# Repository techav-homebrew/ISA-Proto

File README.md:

# ISA-Proto
8-bit ISA Protoboard

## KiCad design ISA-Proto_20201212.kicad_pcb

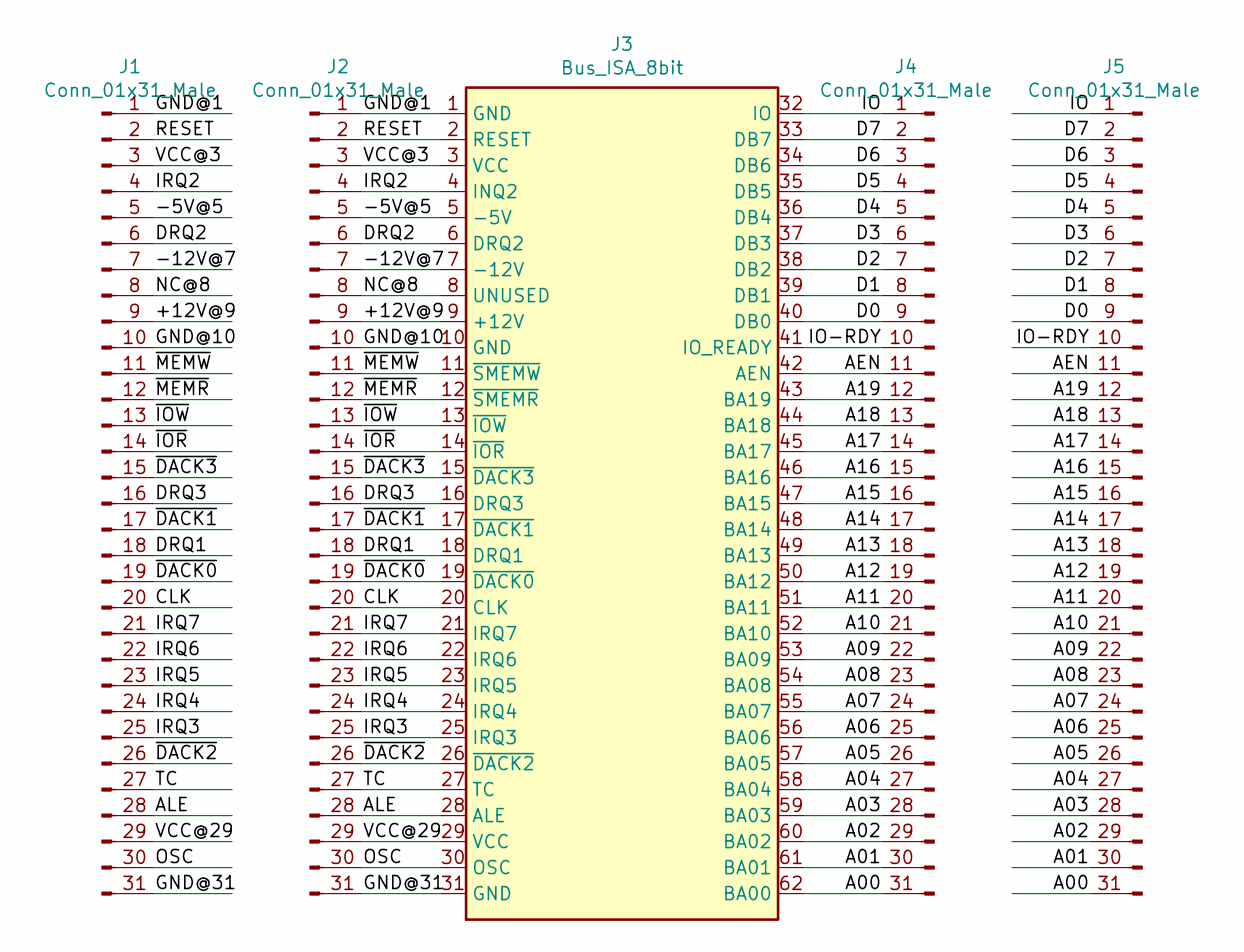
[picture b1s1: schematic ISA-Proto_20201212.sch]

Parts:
J1, J2, J4, J5: Conn_01x31_Male; PinHeader_1x31_P2.54mm_Vertical
J3: Bus_ISA_8bit; BUS_XT

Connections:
/+12V@9: J1.9, J2.9, J3.9 (+12V)
/-5V@5: J1.5, J2.5, J3.5 (-5V)
/-12V@7: J1.7, J2.7, J3.7 (-12V)
/A00: J3.62 (BA00), J4.31, J5.31
/A01: J3.61 (BA01), J4.30, J5.30
/A02: J3.60 (BA02), J4.29, J5.29
/A03: J3.59 (BA03), J4.28, J5.28
/A04: J3.58 (BA04), J4.27, J5.27
/A05: J3.57 (BA05), J4.26, J5.26
/A06: J3.56 (BA06), J4.25, J5.25
/A07: J3.55 (BA07), J4.24, J5.24
/A08: J3.54 (BA08), J4.23, J5.23
/A09: J3.53 (BA09), J4.22, J5.22
/A10: J3.52 (BA10), J4.21, J5.21
/A11: J3.51 (BA11), J4.20, J5.20
/A12: J3.50 (BA12), J4.19, J5.19
/A13: J3.49 (BA13), J4.18, J5.18
/A14: J3.48 (BA14), J4.17, J5.17
/A15: J3.47 (BA15), J4.16, J5.16
/A16: J3.46 (BA16), J4.15, J5.15
/A17: J3.45 (BA17), J4.14, J5.14
/A18: J3.44 (BA18), J4.13, J5.13
/A19: J3.43 (BA19), J4.12, J5.12
/AEN: J3.42 (AEN), J4.11, J5.11
/ALE: J1.28, J2.28, J3.28 (ALE)
/CLK: J1.20, J2.20, J3.20 (CLK)
/D0: J3.40 (DB0), J4.9, J5.9
/D1: J3.39 (DB1), J4.8, J5.8
/D2: J3.38 (DB2), J4.7, J5.7
/D3: J3.37 (DB3), J4.6, J5.6
/D4: J3.36 (DB4), J4.5, J5.5
/D5: J3.35 (DB5), J4.4, J5.4
/D6: J3.34 (DB6), J4.3, J5.3
/D7: J3.33 (DB7), J4.2, J5.2
/DRQ1: J1.18, J2.18, J3.18 (DRQ1)
/DRQ2: J1.6, J2.6, J3.6 (DRQ2)
/DRQ3: J1.16, J2.16, J3.16 (DRQ3)
/GND@1: J1.1, J2.1, J3.1 (GND)
/GND@10: J1.10, J2.10, J3.10 (GND)
/GND@31: J1.31, J2.31, J3.31 (GND)
/IO-RDY: J3.41 (IO_READY), J4.10, J5.10
/IOCHCK: J3.32 (IO), J4.1, J5.1
/IRQ2: J1.4, J2.4, J3.4 (INQ2)
/IRQ3: J1.25, J2.25, J3.25 (IRQ3)
/IRQ4: J1.24, J2.24, J3.24 (IRQ4)
/IRQ5: J1.23, J2.23, J3.23 (IRQ5)
/IRQ6: J1.22, J2.22, J3.22 (IRQ6)
/IRQ7: J1.21, J2.21, J3.21 (IRQ7)
/OSC: J1.30, J2.30, J3.30 (OSC)
/RESET: J1.2, J2.2, J3.2 (RESET)
/TC: J1.27, J2.27, J3.27 (TC)
/VCC@3: J1.3, J2.3, J3.3 (VCC)
/VCC@29: J1.29, J2.29, J3.29 (VCC)
/~CARD: J1.8, J2.8, J3.8 (UNUSED)
/~DACK0: J1.19, J2.19, J3.19 (~DACK0)
/~DACK1: J1.17, J2.17, J3.17 (~DACK1)
/~DACK2: J1.26, J2.26, J3.26 (~DACK2)
/~DACK3: J1.15, J2.15, J3.15 (~DACK3)
/~IOR: J1.14, J2.14, J3.14 (~IOR)
/~IOW: J1.13, J2.13, J3.13 (~IOW)
/~MEMR: J1.12, J2.12, J3.12 (~SMEMR)
/~MEMW: J1.11, J2.11, J3.11 (~SMEMW)

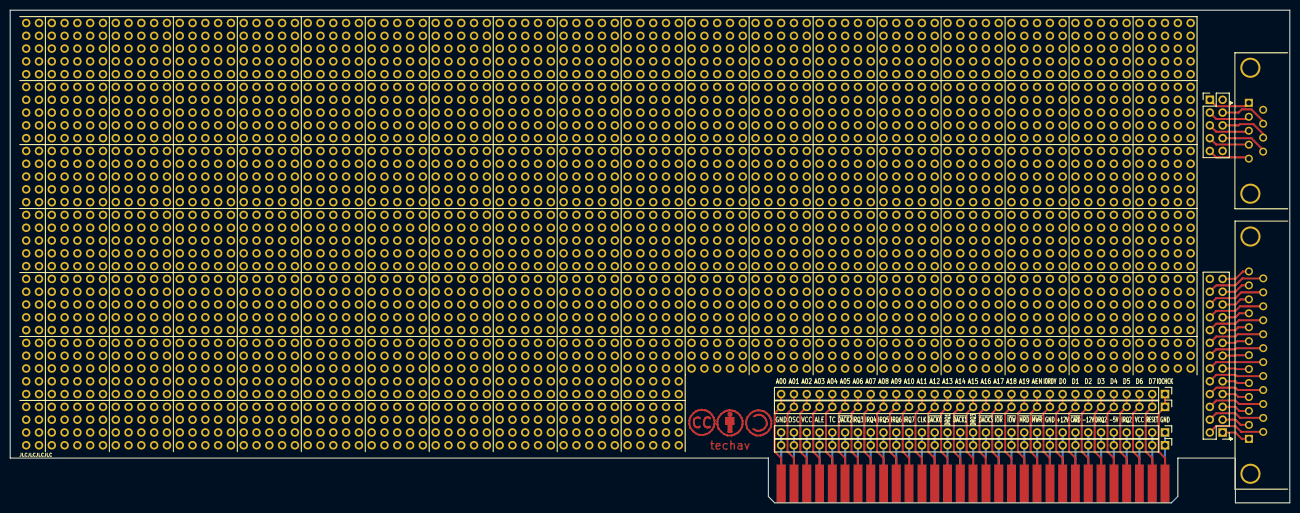
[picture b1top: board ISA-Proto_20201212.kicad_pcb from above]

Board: 2 copper layers, 254.0 x 97.8 mm, 5 parts (0 on the bottom side), 62 nets.
